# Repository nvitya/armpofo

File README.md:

# armpofo
Atari Portfolio Reloaded with ARM Cortex-M

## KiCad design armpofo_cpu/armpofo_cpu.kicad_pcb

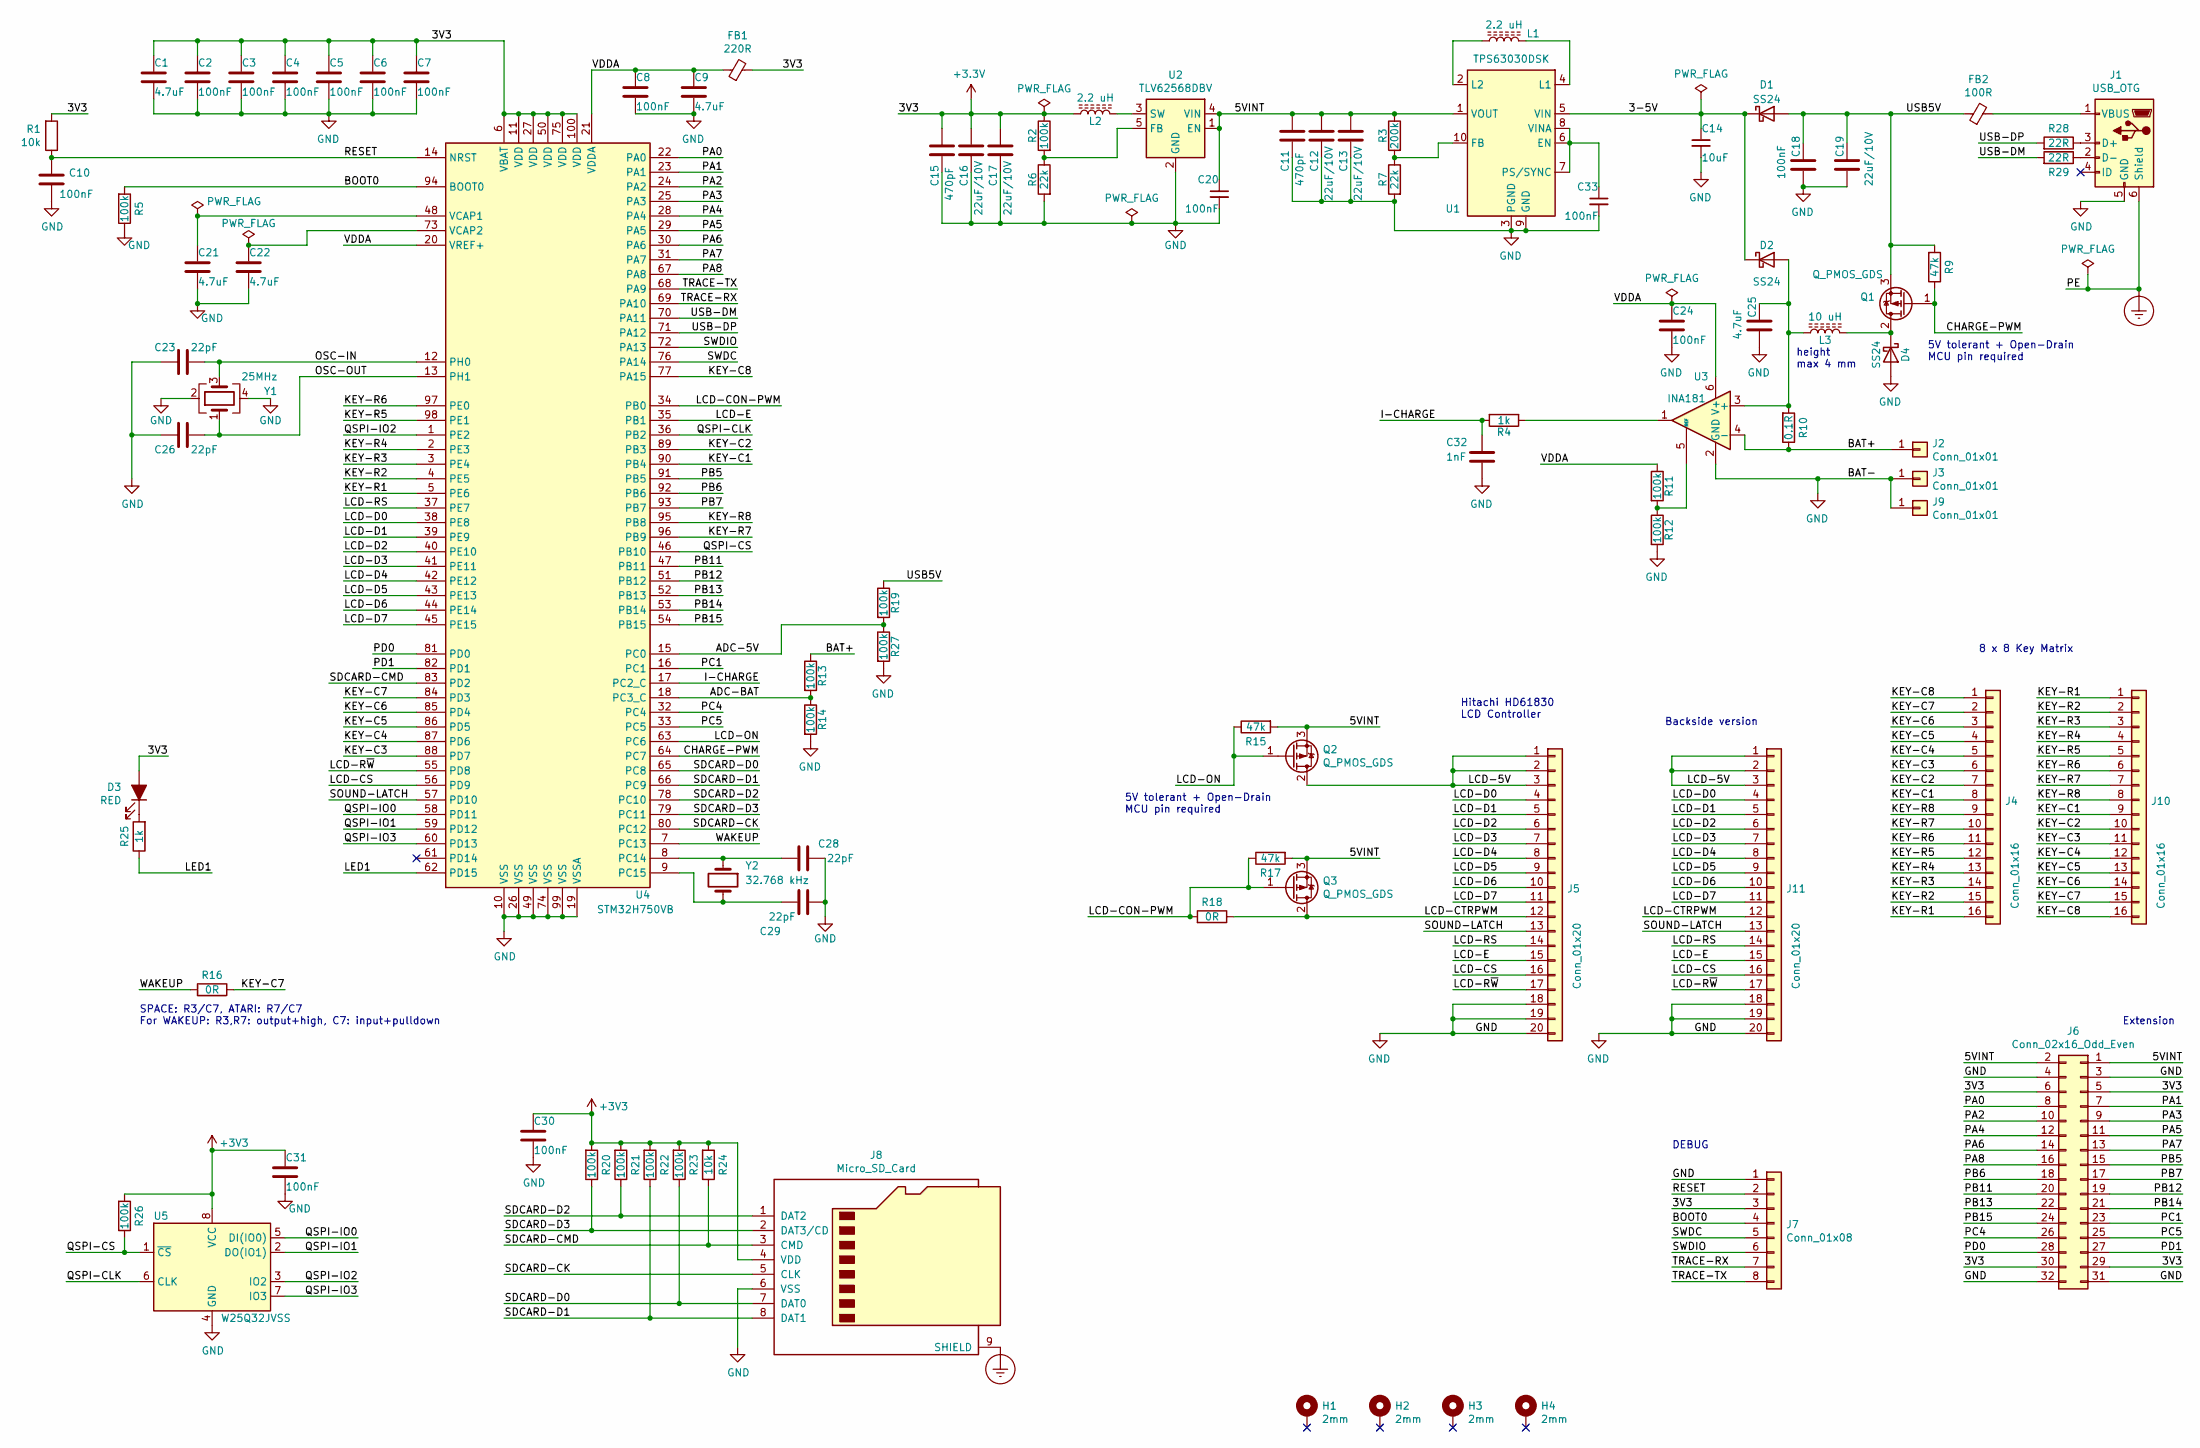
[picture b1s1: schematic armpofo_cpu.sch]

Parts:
C1, C9, C21, C22, C25: 4.7uF; C_0603_1608Metric
C2, C3, C4, C5, C6, C7, C8, C10, C18, C20, C24, C30, C31, C33: 100nF; C_0603_1608Metric
C11, C15: 470pF; C_0603_1608Metric
C12, C13, C16, C17, C19: 22uF/10V; C_1210_3225Metric
C14: 10uF; C_1210_3225Metric
C23, C26, C28, C29: 22pF; C_0603_1608Metric
C32: 1nF; C_0603_1608Metric
D1, D2, D4: SS24; D_1206_3216Metric
D3: RED; D_0603_1608Metric
FB1: 220R; L_0603_1608Metric
FB2: 100R; L_0603_1608Metric
H1, H2, H3, H4: 2mm; MountingHole_2.2mm_M2_DIN965_Pad
J1: USB_OTG; USB_Micro-B_Molex-105017-0001
J2, J3, J9: Conn_01x01; PinHeader_1x01_P2.54mm_Vertical
J4: Conn_01x16; TE_1-84953-6_1x16-1MP_P1.0mm_Horizontal
J5, J11: Conn_01x20; TE_2-84952-0_1x20-1MP_P1.0mm_Horizontal
J6: Conn_02x16_Odd_Even; Conn_Edge_PinSocket_2x16_2.54mm
J7: Conn_01x08; PinHeader_1x08_P2.54mm_Horizontal
J8: Micro_SD_Card; Conn_uSDcard
J10: Conn_01x16; PinHeader_1x16_P1.27mm_Vertical
L1, L2: 2.2 uH; L_Taiyo-Yuden_NR-40xx_HandSoldering
L3: 10 uH; L_Taiyo-Yuden_NR-40xx_HandSoldering
Q1, Q2, Q3: Q_PMOS_GDS; SOT-23
R1, R24: 10k; R_0603_1608Metric
R2, R5, R11, R12, R13, R14, R19, R20, R21, R22, R23, R26, R27: 100k; R_0603_1608Metric
R3: 200k; R_0603_1608Metric
R4, R25: 1k; R_0603_1608Metric
R6, R7: 22k; R_0603_1608Metric
R9, R15, R17: 47k; R_0603_1608Metric
R10: 0.1R; R_1206_3216Metric
R16, R18: 0R; R_0603_1608Metric
R28, R29: 22R; R_0603_1608Metric
U1: TPS63030DSK; WSON-10-1EP_2.5x2.5mm_P0.5mm_EP1.2x2mm
U2: TLV62568DBV; SOT-23-5
U3: INA181; SOT-23-6
U4: STM32H750VB; LQFP-100_14x14mm_P0.5mm
U5: W25Q32JVSS; SO-8_5.3x6.2mm_P1.27mm
Y1: 25MHz; Crystal_SMD_3225-4Pin_3.2x2.5mm
Y2: 32.768 kHz; Crystal_DS26_D2.0mm_L6.0mm_Horizontal_1EP_style1

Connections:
/3-5V: C14.1, D1.1 (K), D2.1 (K), U1.5 (VIN)
/5VINT: C11.1, C12.1, C13.1, C20.1, J6.1, J6.2, Q2.3 (S), Q3.3 (S), R3.1, R15.2, R17.2, U1.1 (VOUT), U2.1 (EN), U2.4 (VIN)
/ADC-5V: R19.2, R27.1, U4.15 (PC0)
/ADC-BAT: R13.2, R14.1, U4.18 (PC3_C)
/BAT+: J2.1, R10.1, R13.1, U3.4 (-)
/BOOT0: J7.4, R5.2, U4.94 (BOOT0)
/CHARGE-PWM: Q1.1 (G), R9.1, U4.64 (PC7)
/I-CHARGE: C32.1, R4.2, U4.17 (PC2_C)
/KEY-C1: J4.8, J10.9, U4.90 (PB4)
/KEY-C2: J4.7, J10.10, U4.89 (PB3)
/KEY-C3: J4.6, J10.11, U4.88 (PD7)
/KEY-C4: J4.5, J10.12, U4.87 (PD6)
/KEY-C5: J4.4, J10.13, U4.86 (PD5)
/KEY-C6: J4.3, J10.14, U4.85 (PD4)
/KEY-C7: J4.2, J10.15, R16.1, U4.84 (PD3)
/KEY-C8: J4.1, J10.16, U4.77 (PA15)
/KEY-R1: J4.16, J10.1, U4.5 (PE6)
/KEY-R2: J4.15, J10.2, U4.4 (PE5)
/KEY-R3: J4.14, J10.3, U4.3 (PE4)
/KEY-R4: J4.13, J10.4, U4.2 (PE3)
/KEY-R5: J4.12, J10.5, U4.98 (PE1)
/KEY-R6: J4.11, J10.6, U4.97 (PE0)
/KEY-R7: J4.10, J10.7, U4.96 (PB9)
/KEY-R8: J4.9, J10.8, U4.95 (PB8)
/LCD-5V: J5.1, J5.2, J5.3, J11.1, J11.2, J11.3, Q2.2 (D)
/LCD-CON-PWM: Q3.1 (G), R17.1, R18.2, U4.34 (PB0)
/LCD-CS: J5.16, J11.16, U4.56 (PD9)
/LCD-CTRPWM: J5.12, J11.12, Q3.2 (D), R18.1
/LCD-D0: J5.4, J11.4, U4.38 (PE8)
/LCD-D1: J5.5, J11.5, U4.39 (PE9)
/LCD-D2: J5.6, J11.6, U4.40 (PE10)
/LCD-D3: J5.7, J11.7, U4.41 (PE11)
/LCD-D4: J5.8, J11.8, U4.42 (PE12)
/LCD-D5: J5.9, J11.9, U4.43 (PE13)
/LCD-D6: J5.10, J11.10, U4.44 (PE14)
/LCD-D7: J5.11, J11.11, U4.45 (PE15)
/LCD-E: J5.15, J11.15, U4.35 (PB1)
/LCD-ON: Q2.1 (G), R15.1, U4.63 (PC6)
/LCD-RS: J5.14, J11.14, U4.37 (PE7)
/LCD-R~W: J5.17, J11.17, U4.55 (PD8)
/LED1: R25.1, U4.62 (PD15)
/OSC-IN: C23.1, U4.12 (PH0), Y1.3
/OSC-OUT: C26.1, U4.13 (PH1), Y1.1
/PA0: J6.8, U4.22 (PA0)
/PA1: J6.7, U4.23 (PA1)
/PA2: J6.10, U4.24 (PA2)
/PA3: J6.9, U4.25 (PA3)
/PA4: J6.12, U4.28 (PA4)
/PA5: J6.11, U4.29 (PA5)
/PA6: J6.14, U4.30 (PA6)
/PA7: J6.13, U4.31 (PA7)
/PA8: J6.16, U4.67 (PA8)
/PB5: J6.15, U4.91 (PB5)
/PB6: J6.18, U4.92 (PB6)
/PB7: J6.17, U4.93 (PB7)
/PB11: J6.20, U4.47 (PB11)
/PB12: J6.19, U4.51 (PB12)
/PB13: J6.22, U4.52 (PB13)
/PB14: J6.21, U4.53 (PB14)
/PB15: J6.24, U4.54 (PB15)
/PC1: J6.23, U4.16 (PC1)
/PC4: J6.26, U4.32 (PC4)
/PC5: J6.25, U4.33 (PC5)
/PD0: J6.28, U4.81 (PD0)
/PD1: J6.27, U4.82 (PD1)
/QSPI-CLK: U4.36 (PB2), U5.6 (CLK)
/QSPI-CS: R26.1, U4.46 (PB10), U5.1 (~CS)
/QSPI-IO0: U4.58 (PD11), U5.5 (DI(IO0))
/QSPI-IO1: U4.59 (PD12), U5.2 (DO(IO1))
/QSPI-IO2: U4.1 (PE2), U5.3 (IO2)
/QSPI-IO3: U4.60 (PD13), U5.7 (IO3)
/RESET: C10.1, J7.2, R1.1, U4.14 (NRST)
/SDCARD-CK: J8.5 (CLK), U4.80 (PC12)
/SDCARD-CMD: J8.3 (CMD), R24.1, U4.83 (PD2)
/SDCARD-D0: J8.7 (DAT0), R23.1, U4.65 (PC8)
/SDCARD-D1: J8.8 (DAT1), R22.1, U4.66 (PC9)
/SDCARD-D2: J8.1 (DAT2), R21.1, U4.78 (PC10)
/SDCARD-D3: J8.2 (DAT3/CD), R20.1, U4.79 (PC11)
/SOUND-LATCH: J5.13, J11.13, U4.57 (PD10)
/SWDC: J7.5, U4.76 (PA14)
/SWDIO: J7.6, U4.72 (PA13)
/TRACE-RX: J7.7, U4.69 (PA10)
/TRACE-TX: J7.8, U4.68 (PA9)
/USB5V: C18.1, C19.1, D1.2 (A), FB2.1, Q1.3 (S), R9.2, R19.1
/USB-DM: R29.2, U4.70 (PA11)
/USB-DP: R28.2, U4.71 (PA12)
/VDDA: C8.1, C9.1, C24.1, FB1.1, R11.1, U3.6 (V+), U4.20 (VREF+), U4.21 (VDDA)
/WAKEUP: R16.2, U4.7 (PC13)
Earth_Protective: J1.6 (Shield), J8.9 (SHIELD)
GND: C1.2, C2.2, C3.2, C4.2, C5.2, C6.2, C7.2, C8.2, C9.2, C10.2, C11.2, C12.2, C13.2, C14.2, C15.2, C16.2, C17.2, C18.2, C19.2, C20.2, C21.2, C22.2, C23.2, C24.2, C25.2, C26.2, C28.2, C29.2, C30.2, C31.2, C32.2, C33.2, D4.2 (A), J1.5 (GND), J3.1, J5.18, J5.19, J5.20, J6.3, J6.4, J6.31, J6.32, J7.1, J8.6 (VSS), J9.1, J11.18, J11.19, J11.20, R5.1, R6.2, R7.2, R12.2, R14.2, R27.2, U1.3 (PGND), U1.9 (GND), U1.11 (PGND), U2.2 (GND), U3.2 (GND), U4.10 (VSS), U4.19 (VSSA), U4.26 (VSS), U4.49 (VSS), U4.74 (VSS), U4.99 (VSS), U5.4 (GND), Y1.2, Y1.4
unnamed: C21.1, U4.48 (VCAP1)
unnamed: C22.1, U4.73 (VCAP2)
unnamed: C25.1, D2.2 (A), L3.2, R10.2, U3.3 (+)
unnamed: C28.1, U4.8 (PC14), Y2.1
unnamed: C29.1, U4.9 (PC15), Y2.2
unnamed: C33.1, U1.6 (EN), U1.7 (PS/SYNC), U1.8 (VINA)
unnamed: D3.1 (K), R25.2
unnamed: D4.1 (K), L3.1, Q1.2 (D)
unnamed: FB2.2, J1.1 (VBUS)
unnamed: J1.2 (D-), R29.1
unnamed: J1.3 (D+), R28.1
unnamed: L1.1, U1.4 (L1)
unnamed: L1.2, U1.2 (L2)
unnamed: L2.1, U2.3 (SW)
unnamed: R2.2, R6.1, U2.5 (FB)
unnamed: R3.2, R7.1, U1.10 (FB)
unnamed: R4.1, U3.1
unnamed: R11.2, R12.1, U3.5 (REF)

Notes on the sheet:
Hitachi HD61830 LCD Controller
8 x 8 Key Matrix
Extension
DEBUG
5V tolerant + Open-Drain MCU pin required
height max 4 mm
SPACE: R3/C7, ATARI: R7/C7 For WAKEUP: R3,R7: output+high, C7: input+pulldown
Backside version

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
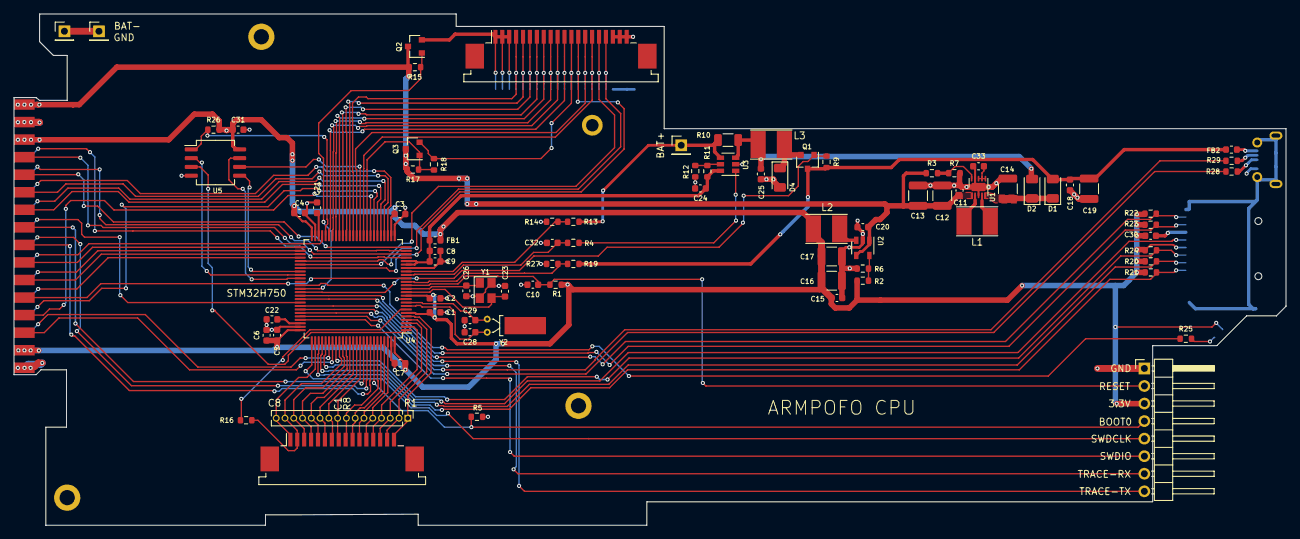
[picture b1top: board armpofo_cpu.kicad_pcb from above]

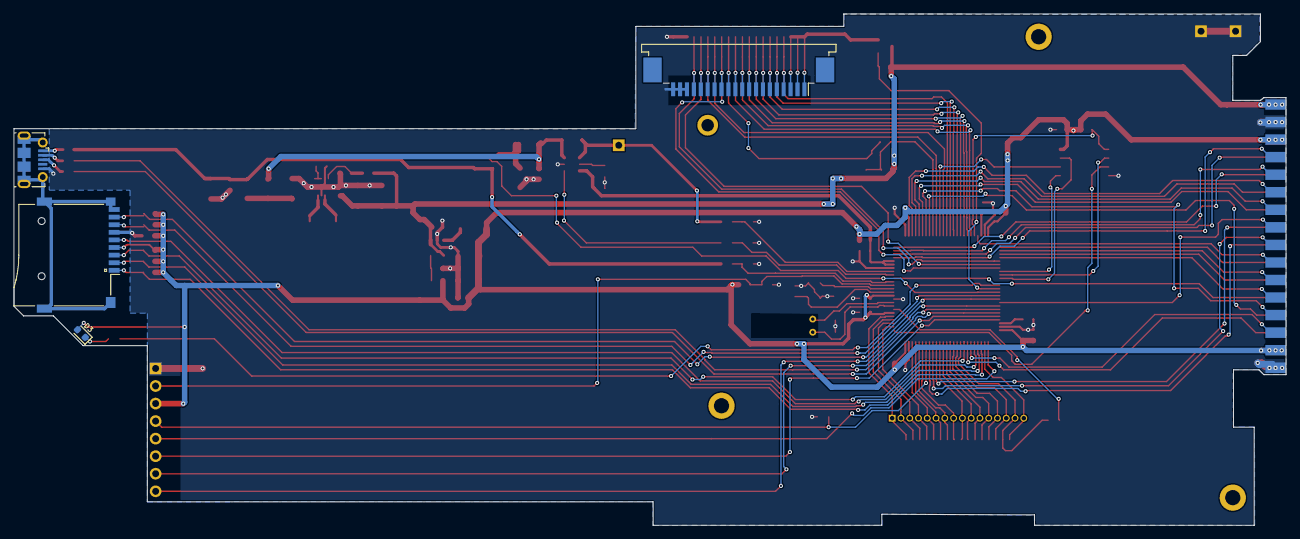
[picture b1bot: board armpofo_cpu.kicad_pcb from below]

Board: 2 copper layers, 184.1 x 74.0 mm, 94 parts (4 on the bottom side), 109 nets.

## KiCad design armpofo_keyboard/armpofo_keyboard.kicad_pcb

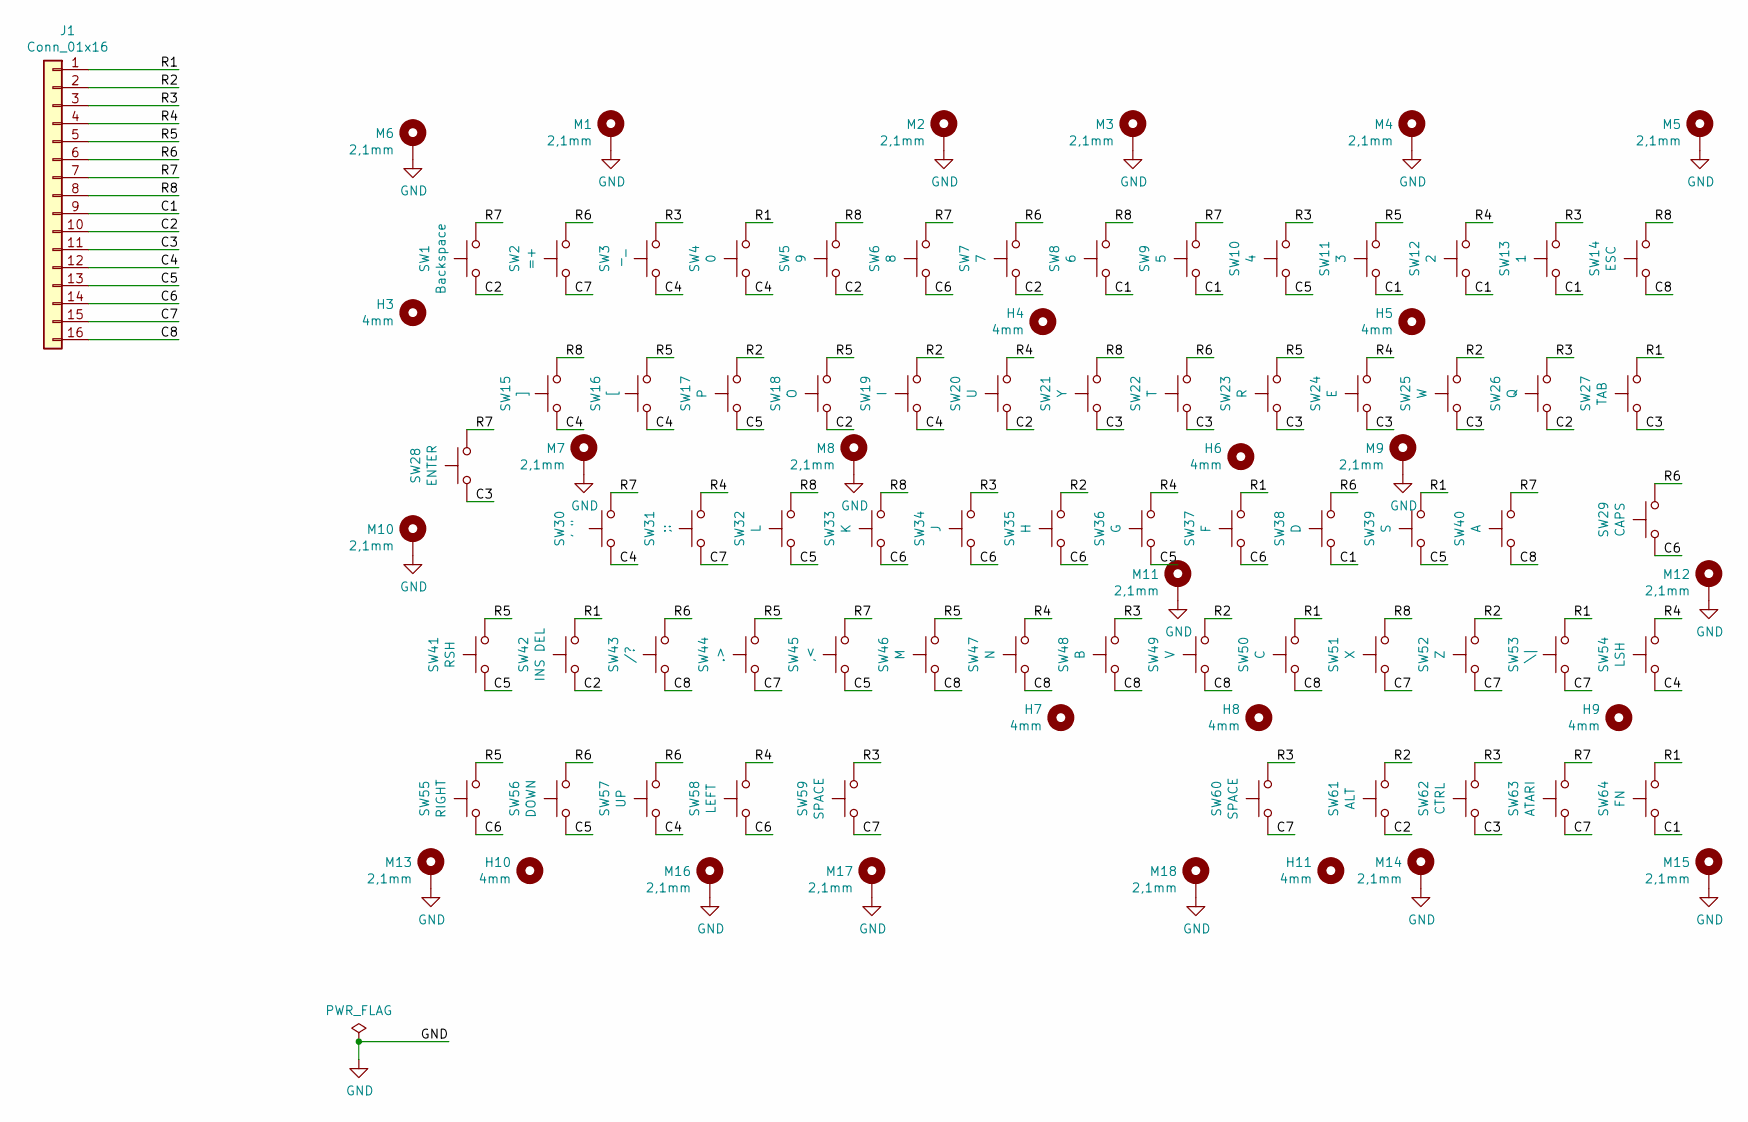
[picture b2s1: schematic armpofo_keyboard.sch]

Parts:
H3, H4, H5, H6, H7, H8, H9, H10, H11: 4mm; MountingHole_4mm
J1: Conn_01x16; TE_1-84953-6_1x16-1MP_P1.0mm_Horizontal
M1, M2, M3, M4, M5, M6, M7, M8, M9, M10, M11, M12, M13, M14, M15, M16, M17, M18: 2,1mm; MountingHole_2.2mm_M2_DIN965_Pad
SW1: Backspace; Key_landing
SW2: =+; Key_landing
SW3: -_; Key_landing
SW4: 0; Key_landing
SW5: 9; Key_landing
SW6: 8; Key_landing
SW7: 7; Key_landing
SW8: 6; Key_landing
SW9: 5; Key_landing
SW10: 4; Key_landing
SW11: 3; Key_landing
SW12: 2; Key_landing
SW13: 1; Key_landing
SW14: ESC; Key_landing
SW15: ]; Key_landing
SW16: [; Key_landing
SW17: P; Key_landing
SW18: O; Key_landing
SW19: I; Key_landing
SW20: U; Key_landing
SW21: Y; Key_landing
SW22: T; Key_landing
SW23: R; Key_landing
SW24: E; Key_landing
SW25: W; Key_landing
SW26: Q; Key_landing
SW27: TAB; Key_landing
SW28: ENTER; Key_landing
SW29: CAPS; Key_landing
SW30: ' \"; Key_landing
SW31: ;:; Key_landing
SW32: L; Key_landing
SW33: K; Key_landing
SW34: J; Key_landing
SW35: H; Key_landing
SW36: G; Key_landing
SW37: F; Key_landing
SW38: D; Key_landing
SW39: S; Key_landing
SW40: A; Key_landing
SW41: RSH; Key_landing
SW42: INS DEL; Key_landing
SW43: /?; Key_landing
SW44: .>; Key_landing
SW45: ,<; Key_landing
SW46: M; Key_landing
SW47: N; Key_landing
SW48: B; Key_landing
SW49: V; Key_landing
SW50: C; Key_landing
SW51: X; Key_landing
SW52: Z; Key_landing
SW53: \\|; Key_landing
SW54: LSH; Key_landing
SW55: RIGHT; Key_landing
SW56: DOWN; Key_landing
SW57: UP; Key_landing
SW58: LEFT; Key_landing
SW59, SW60: SPACE; Key_landing
SW61: ALT; Key_landing
SW62: CTRL; Key_landing
SW63: ATARI; Key_landing
SW64: FN; Key_landing

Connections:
/C1: J1.9, SW8.2, SW9.2, SW11.2, SW12.2, SW13.2, SW38.2, SW64.2
/C2: J1.10, SW1.2, SW5.2, SW7.2, SW18.2, SW20.2, SW26.2, SW42.2, SW61.2
/C3: J1.11, SW21.2, SW22.2, SW23.2, SW24.2, SW25.2, SW27.2, SW28.2, SW62.2
/C4: J1.12, SW3.2, SW4.2, SW15.2, SW16.2, SW19.2, SW30.2, SW54.2, SW57.2
/C5: J1.13, SW10.2, SW17.2, SW32.2, SW36.2, SW39.2, SW41.2, SW45.2, SW56.2
/C6: J1.14, SW6.2, SW29.2, SW33.2, SW34.2, SW35.2, SW37.2, SW55.2, SW58.2
/C7: J1.15, SW2.2, SW31.2, SW44.2, SW51.2, SW52.2, SW53.2, SW59.2, SW60.2, SW63.2
/C8: J1.16, SW14.2, SW40.2, SW43.2, SW46.2, SW47.2, SW48.2, SW49.2, SW50.2
/R1: J1.1, SW4.1, SW27.1, SW37.1, SW39.1, SW42.1, SW50.1, SW53.1, SW64.1
/R2: J1.2, SW17.1, SW19.1, SW25.1, SW35.1, SW49.1, SW52.1, SW61.1
/R3: J1.3, SW3.1, SW10.1, SW13.1, SW26.1, SW34.1, SW48.1, SW59.1, SW60.1, SW62.1
/R4: J1.4, SW12.1, SW20.1, SW24.1, SW31.1, SW36.1, SW47.1, SW54.1, SW58.1
/R5: J1.5, SW11.1, SW16.1, SW18.1, SW23.1, SW41.1, SW44.1, SW46.1, SW55.1
/R6: J1.6, SW2.1, SW7.1, SW22.1, SW29.1, SW38.1, SW43.1, SW56.1, SW57.1
/R7: J1.7, SW1.1, SW6.1, SW9.1, SW28.1, SW30.1, SW40.1, SW45.1, SW63.1
/R8: J1.8, SW5.1, SW8.1, SW14.1, SW15.1, SW21.1, SW32.1, SW33.1, SW51.1
GND: M1.1, M2.1, M3.1, M4.1, M5.1, M6.1, M7.1, M8.1, M9.1, M10.1, M11.1, M12.1, M13.1, M14.1, M15.1, M16.1, M17.1, M18.1

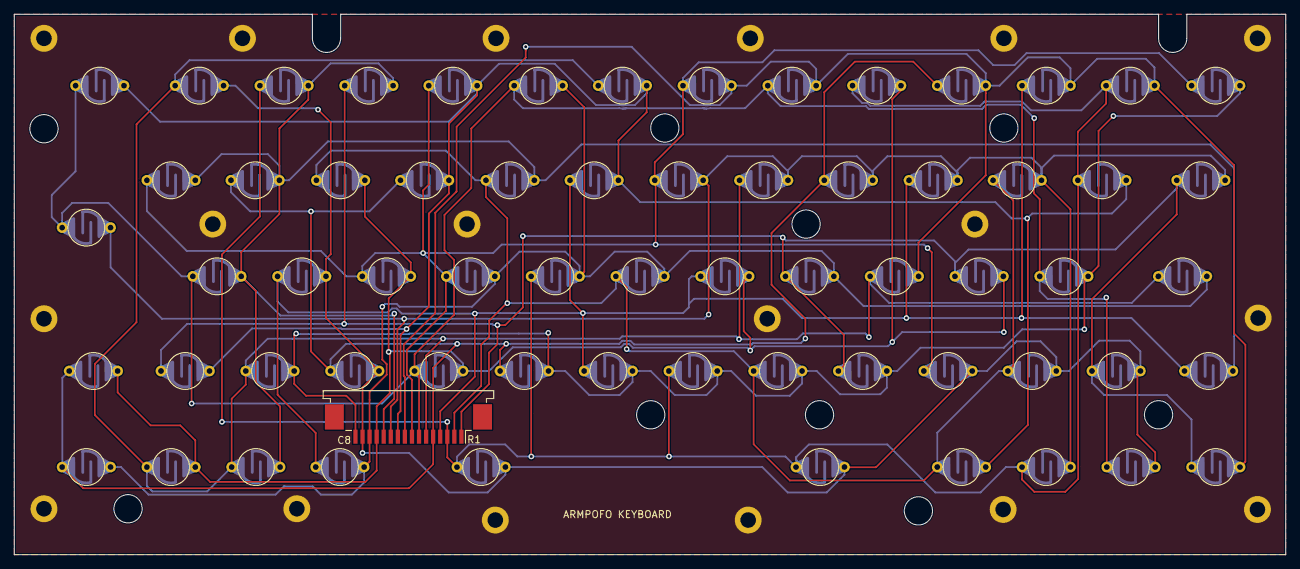
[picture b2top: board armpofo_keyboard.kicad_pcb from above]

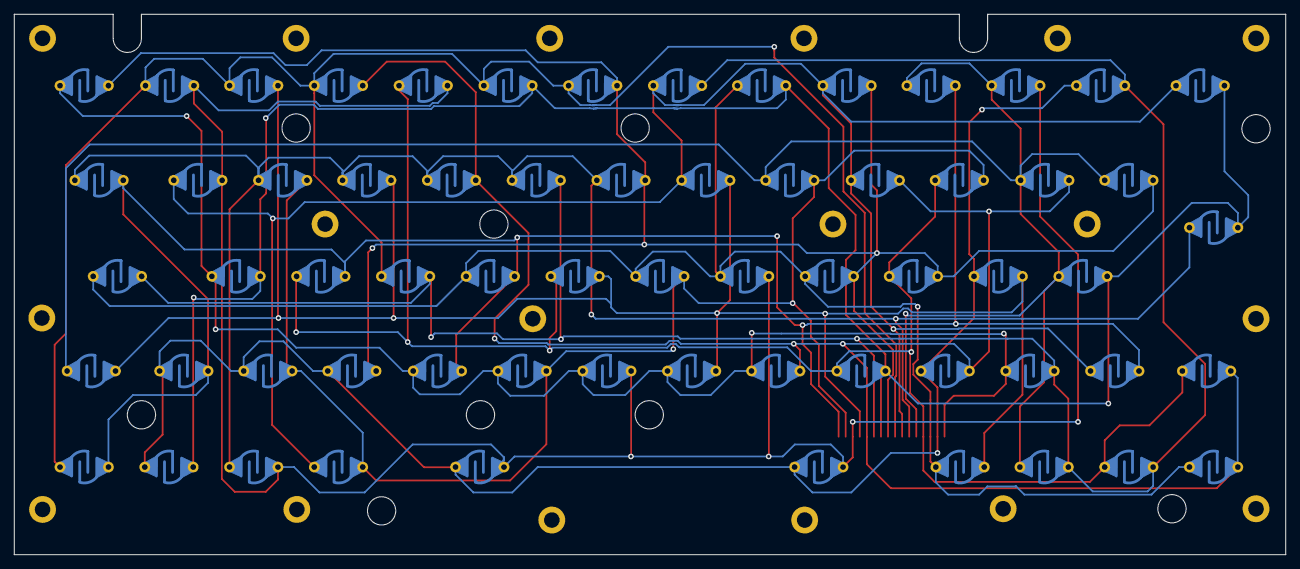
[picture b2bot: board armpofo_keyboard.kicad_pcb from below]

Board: 2 copper layers, 180.0 x 76.5 mm, 92 parts (64 on the bottom side), 17 nets.

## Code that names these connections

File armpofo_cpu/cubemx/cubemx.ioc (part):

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PD12.GPIO_Label=QSPI-IO1
PA15\ (JTDI).GPIOParameters=GPIO_Label
PE11.GPIOParameters=GPIO_Label
PB10.Mode=Single Bank 1
PC12.Signal=SDMMC1_CK
PD3.GPIOParameters=GPIO_Label
PA15\ (JTDI).Signal=GPIO_Output
PD2.GPIOParameters=GPIO_Label
PC5.Mode=RMII
PB3\ (JTDO/TRACESWO).GPIOParameters=GPIO_Label
PB13.Signal=ETH_TXD1
PD6.GPIO_Label=KEY-R5
PE6.GPIO_Label=KEY-C8
PA14\ (JTCK/SWCLK).Signal=DEBUG_JTCK-SWCLK
PE2.Mode=Single Bank 1
PD4.Signal=GPIO_Output
PB6.Signal=FDCAN2_TX
PB6.Mode=FDCANSlave
PD0.Signal=FDCAN1_RX
PD8.Signal=GPIO_Output
PE5.Signal=GPIO_Output
PE1.Signal=GPIO_Output
PD1.Stacked=true
PA2.Stacked=true
PB2.Signal=QUADSPI_CLK
PB0.GPIOParameters=GPIO_Label
PA13\ (JTMS/SWDIO).GPIO_Label=SWDIO
PE0.GPIOParameters=GPIO_Label
PE9.Signal=GPIO_Output
PB14.Mode=Device_Only_FS
PB1.GPIO_Label=LCD-E
PE4.GPIO_Label=KEY-C6
PC9.Mode=SD_4_bits_Wide_bus
PE2.Signal=QUADSPI_BK1_IO2
PA8.Signal=RCC_MCO_1
PA14\ (JTCK/SWCLK).Mode=Serial_Wire
PE10.Signal=GPIO_Output
PB14.Stacked=true
PA0.Signal=ADC1_INP16
PC8.GPIOParameters=GPIO_Label
Mcu.Package=LQFP100
PB9.Signal=GPIO_Output
PB1.Signal=GPIO_Output
PE10.GPIOParameters=GPIO_Label
PD12.Signal=QUADSPI_BK1_IO1
PD5.GPIOParameters=GPIO_Label
PC3_C.GPIO_Label=ADC_VBAT
PA10.Signal=USART1_RX
PE12.GPIO_Label=LCD-D4
PC11.Mode=SD_4_bits_Wide_bus
PC14-OSC32_IN\ (OSC32_IN).Mode=LSE-External-Oscillator
PA14\ (JTCK/SWCLK).GPIO_Label=SWDCLK
PB10.GPIOParameters=GPIO_Label
PB13.Mode=RMII
PE10.GPIO_Label=LCD-D2
PH0-OSC_IN\ (PH0).Mode=HSE-External-Oscillator
PB6.Stacked=true
PC4.Mode=RMII
PD6.GPIOParameters=GPIO_Label
PD9.GPIO_Label=LCD-CS
PA9.GPIO_Label=TRACE-TX
PC13.Signal=PWR_WKUP2
PD3.Signal=GPIO_Output
PD13.GPIOParameters=GPIO_Label
PD7.Signal=GPIO_Output
PD1.Signal=FDCAN1_TX
PA11.GPIO_Label=USB-DM
PB7.Stacked=true
PC11.GPIOParameters=GPIO_Label
PD10.Signal=GPIO_Output
PB8.GPIO_Label=KEY-C1
PB11.Mode=RMII
PC3_C.GPIOParameters=GPIO_Label
PE8.GPIO_Label=LCD-D0
PA6.Stacked=true
PA9.Signal=USART1_TX
PE9.GPIO_Label=LCD-D1
PB10.Signal=QUADSPI_BK1_NCS
PB14.Signal=USB_OTG_HS_DM
PA5.Signal=COMP_DAC12_group
PE13.GPIOParameters=GPIO_Label
PC12.Mode=SD_4_bits_Wide_bus
PE1.GPIO_Label=KEY-C4
PD1.Mode=FDCANMaster
PA1.Mode=RMII
PE14.Signal=GPIO_Output
PE15.Signal=GPIO_Output
PE8.Signal=GPIO_Output
PC4.Stacked=true
PC10.GPIOParameters=GPIO_Label
PA5.Stacked=true
PC9.GPIOParameters=GPIO_Label
PD0.Stacked=true
PC8.Mode=SD_4_bits_Wide_bus
PA4.Signal=COMP_DAC11_group
PB5.Signal=FDCAN2_RX
PE13.GPIO_Label=LCD-D5
PD12.Mode=Single Bank 1
PD11.Signal=QUADSPI_BK1_IO0
PE5.GPIO_Label=KEY-C7
PC12.GPIO_Label=SDCARD-CK
PA11.Signal=USB_OTG_FS_DM
PE3.Signal=GPIO_Output
PA8.Mode=Clock-out-1
PB4\ (NJTRST).GPIO_Label=KEY-R8
PE12.GPIOParameters=GPIO_Label
PB15.Stacked=true
PD2.Signal=SDMMC1_CMD
PB0.Signal=GPIO_Output
PC1.Signal=ETH_MDC
PD2.GPIO_Label=SDCARD-CMD
PD7.GPIOParameters=GPIO_Label
PA13\ (JTMS/SWDIO).Signal=DEBUG_JTMS-SWDIO
PC1.Mode=RMII
PA0.Stacked=true
PA14\ (JTCK/SWCLK).GPIOParameters=GPIO_Label
PB13.Stacked=true
Mcu.UserName=STM32H750VBTx
PD9.GPIOParameters=GPIO_Label
PH0-OSC_IN\ (PH0).Signal=RCC_OSC_IN
PA7.Stacked=true
PE11.GPIO_Label=LCD-D3
PC10.Signal=SDMMC1_D2
PC15-OSC32_OUT\ (OSC32_OUT).Mode=LSE-External-Oscillator
PA12.GPIOParameters=GPIO_Label
PA9.GPIOParameters=GPIO_Label
PA11.GPIOParameters=GPIO_Label
PA11.Mode=Device_Only
PB0.GPIO_Label=LCD-CON-PWM
PB11.Signal=ETH_TX_EN
PB15.Signal=USB_OTG_HS_DP
PE5.GPIOParameters=GPIO_Label
PD13.Signal=QUADSPI_BK1_IO3
PA12.Signal=USB_OTG_FS_DP
PE4.GPIOParameters=GPIO_Label
PD11.GPIO_Label=QSPI-IO0
PD8.GPIOParameters=GPIO_Label
PD10.GPIOParameters=GPIO_Label
PH1-OSC_OUT\ (PH1).Mode=HSE-External-Oscillator
PE13.Signal=GPIO_Output
PC11.GPIO_Label=SDCARD-D3
PB5.Mode=FDCANSlave
PA10.GPIO_Label=TRACE-RX
PE3.GPIOParameters=GPIO_Label
PB7.Signal=I2C1_SDA
PE4.Signal=GPIO_Output
PE6.GPIOParameters=GPIO_Label
PA1.Stacked=true
PD7.GPIO_Label=KEY-R6
PD13.GPIO_Label=QSPI-IO3
PA6.Signal=ADCx_INP3
PB12.Mode=RMII
PD5.GPIO_Label=KEY-R4
PC5.Stacked=true
PE0.GPIO_Label=KEY-C3
PC5.Signal=ETH_RXD1
PD3.GPIO_Label=KEY-R2
PE7.Signal=GPIO_Output
PA4.Stacked=true
PD6.Signal=GPIO_Output
PE2.GPIO_Label=QSPI-IO2
PA3.Signal=ADCx_INP15
PB3\ (JTDO/TRACESWO).GPIO_Label=KEY-R7
PE8.GPIOParameters=GPIO_Label
PB8.GPIOParameters=GPIO_Label
PA7.Mode=RMII
PA13\ (JTMS/SWDIO).Mode=Serial_Wire
PE14.GPIOParameters=GPIO_Label
PB9.GPIO_Label=KEY-C2
PA10.Mode=Asynchronous
PC10.GPIO_Label=SDCARD-D2
PC9.GPIO_Label=SDCARD-D1
PC11.Signal=SDMMC1_D3
PC8.Signal=SDMMC1_D0
PC4.Signal=ETH_RXD0
PC10.Mode=SD_4_bits_Wide_bus
PA8.Stacked=true
PA3.Stacked=true
PE14.GPIO_Label=LCD-D6
PD9.Signal=GPIO_Output
PD5.Signal=GPIO_Output
PA13\ (JTMS/SWDIO).GPIOParameters=GPIO_Label
PA12.GPIO_Label=USB-DP
PH1-OSC_OUT\ (PH1).Signal=RCC_OSC_OUT
PE9.GPIOParameters=GPIO_Label
PE15.GPIOParameters=GPIO_Label
PD8.GPIO_Label=LCD-RW
PB9.GPIOParameters=GPIO_Label
PC8.GPIO_Label=SDCARD-D0
PC12.GPIOParameters=GPIO_Label
PA9.Mode=Asynchronous
PB4\ (NJTRST).GPIOParameters=GPIO_Label
PE15.GPIO_Label=LCD-D7
PD12.GPIOParameters=GPIO_Label
PB3\ (JTDO/TRACESWO).Signal=GPIO_Output
PC15-OSC32_OUT\ (OSC32_OUT).Signal=RCC_OSC32_OUT
PB10.GPIO_Label=QSPI-CS
PE7.GPIOParameters=GPIO_Label
PB2.GPIOParameters=GPIO_Label
PD13.Mode=Single Bank 1
PE2.GPIOParameters=GPIO_Label
PD10.GPIO_Label=SOUND-LATCH
PE11.Signal=GPIO_Output
PA1.Signal=ETH_REF_CLK
PD2.Mode=SD_4_bits_Wide_bus
board=custom
PB15.Mode=Device_Only_FS
PD11.GPIOParameters=GPIO_Label
PD4.GPIO_Label=KEY-R3
PA10.GPIOParameters=GPIO_Label
PD4.GPIOParameters=GPIO_Label
PE6.Signal=GPIO_Output
PC13.Mode=WakeUp2
PA15\ (JTDI).GPIO_Label=KEY-R1
Mcu.Name=STM32H750VBTx
PE0.Signal=GPIO_Output
PE7.GPIO_Label=LCD-RS
PD0.Mode=FDCANMaster
PE12.Signal=GPIO_Output
PA2.Signal=ETH_MDIO
PB5.Stacked=true
RCC.SYSCLKFreq_VALUE=64000000
PA12.Mode=Device_Only
PC14-OSC32_IN\ (OSC32_IN).Signal=RCC_OSC32_IN
PB2.Mode=Single Bank 1
PB2.GPIO_Label=QSPI-CLK
PD11.Mode=Single Bank 1
PB12.Stacked=true
PC3_C.Signal=ADC3_INP1
PA2.Mode=RMII
PB8.Signal=GPIO_Output
PE3.GPIO_Label=KEY-C5
PC9.Signal=SDMMC1_D1
PC1.Stacked=true
PB12.Signal=ETH_TXD0
PE1.GPIOParameters=GPIO_Label
PB1.GPIOParameters=GPIO_Label
PA7.Signal=ETH_CRS_DV
PB4\ (NJTRST).Signal=GPIO_Output

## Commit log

2020-10-11 keyboard pcb project added
2020-10-13 some progress with the CPU board
2020-10-17 cpu + ext pins finished
2020-10-17 schematic almost finished
2020-10-18 holes are arranged to their final place
2020-10-19 key landing at the final positions
2020-10-19 small align adjustments
2020-10-19 edge cut correction
2020-10-19 routing finished
2020-10-23 cpu schematic finished
2020-10-25 - CPU board finalisch edge cuts - Keyboard mounting modified to 2.2 mm holes
2020-10-25 final form
2020-10-26 some progress
2020-10-31 routing progress 70%
2020-10-31 routing finished.
2020-11-14 eclipse CDT test project added
2020-11-15 working keyboard test with symbol conversion
2020-11-21 PCB corrections some items moved to the backside
2020-11-21 some keyboard and screen test
2020-11-22 finalizing sizes, positions
2020-11-22 usb overstrecht corrected
2020-11-24 gerber files generated
2020-12-05 HW test project for the assembled STM32H750 Atari Portfolio
2020-12-06 working power-saving, the boost converter requires 5 mA unfortunately
2020-12-08 analogue measurement and battery charging
2020-12-08 some battery monitoring
2020-12-09 calculator fixes
2020-12-10 variable support for the calculator
2020-12-13 working bootloader -> SYS loading
2020-12-13 no adc init at the bootloader
2020-12-19 sw dir reorganization
2020-12-19 fix hwtests structure
2020-12-20 working new application interface
2020-12-21 restructured, calculator is an appication now
2020-12-22 returning from the app call
2020-12-29 bl compile fixes, some simple tests
